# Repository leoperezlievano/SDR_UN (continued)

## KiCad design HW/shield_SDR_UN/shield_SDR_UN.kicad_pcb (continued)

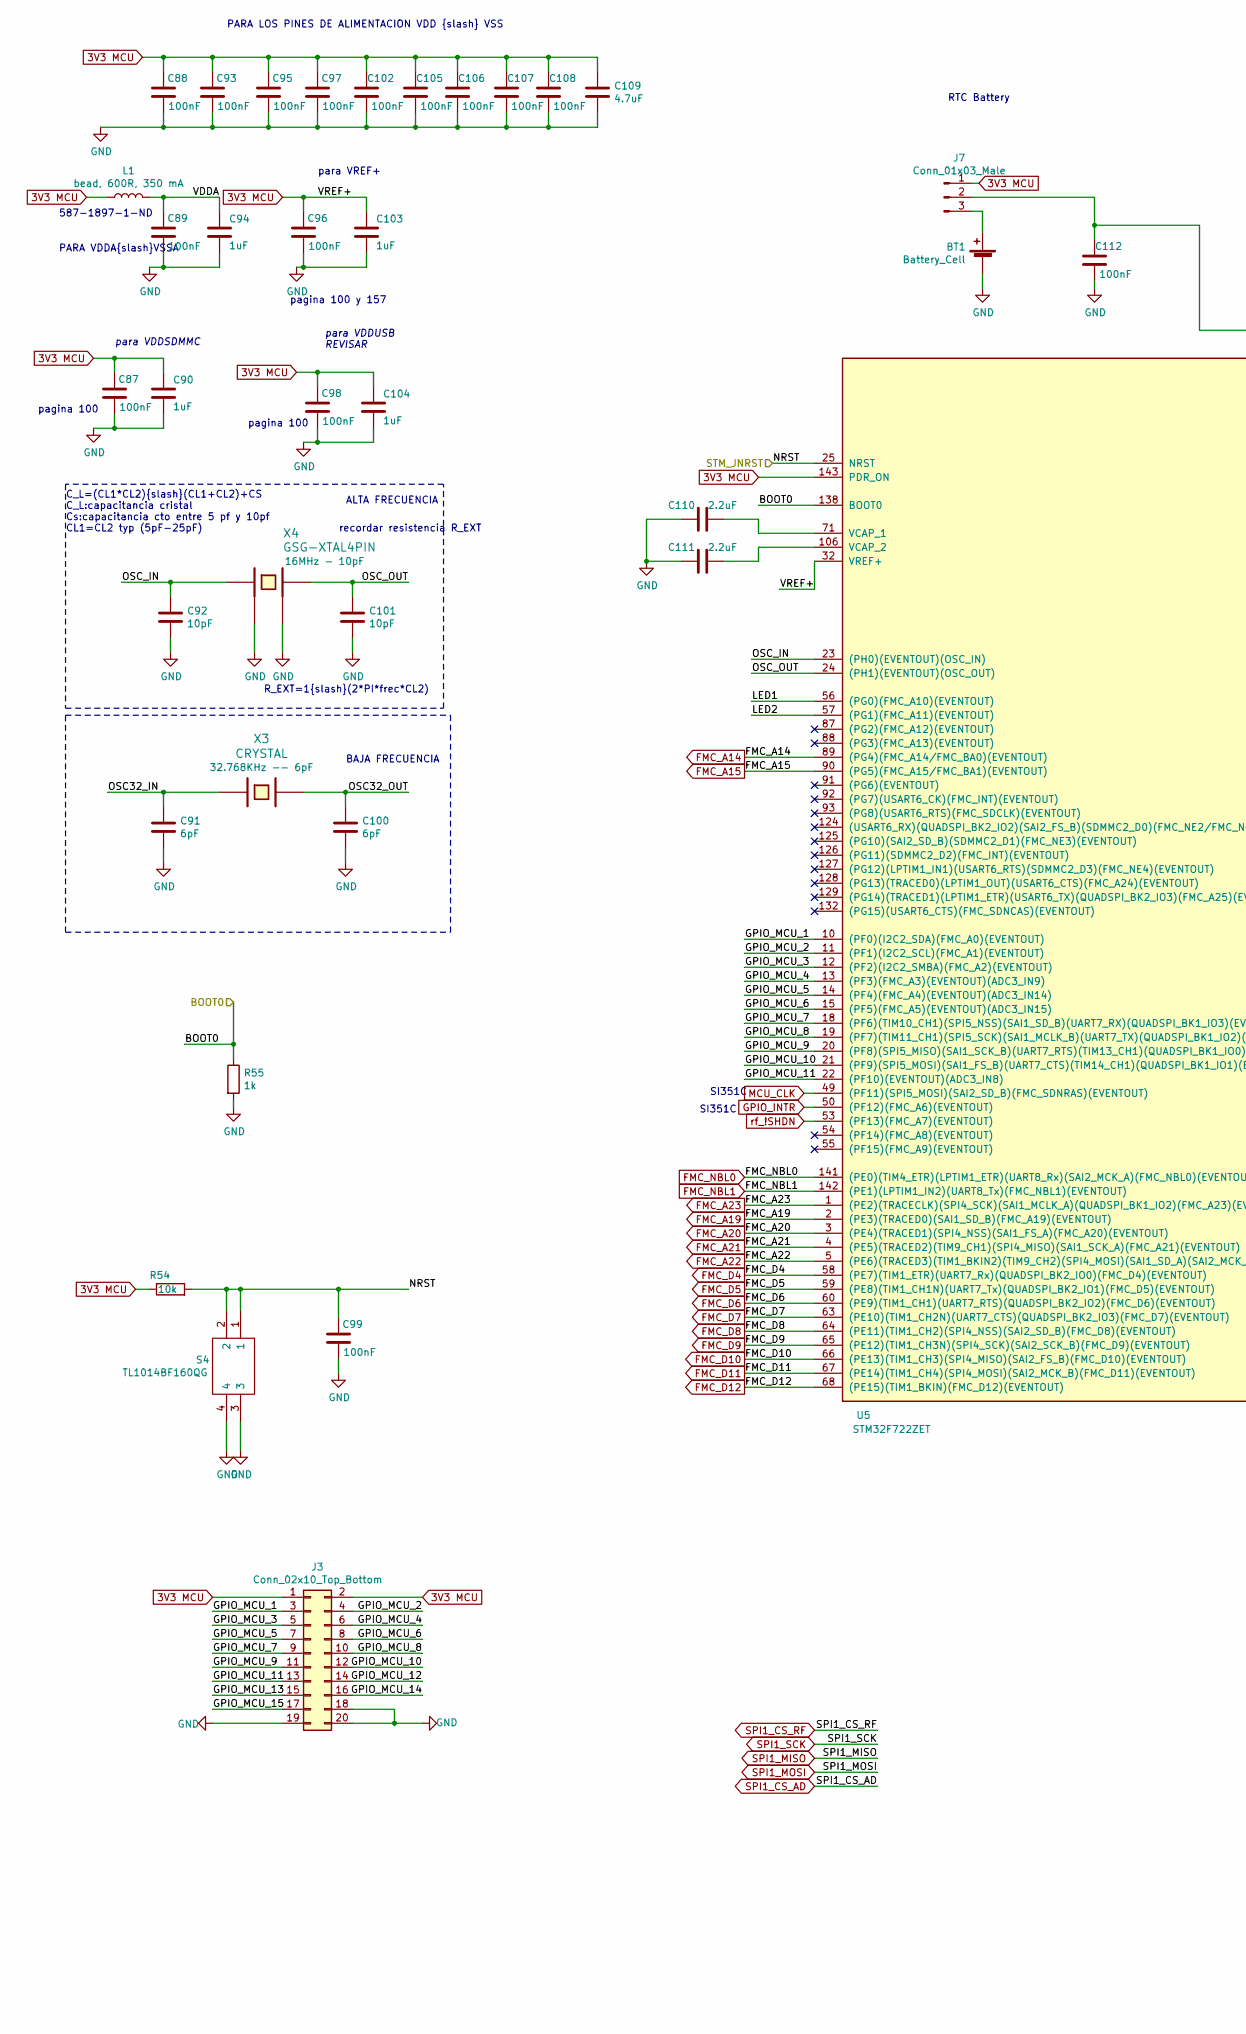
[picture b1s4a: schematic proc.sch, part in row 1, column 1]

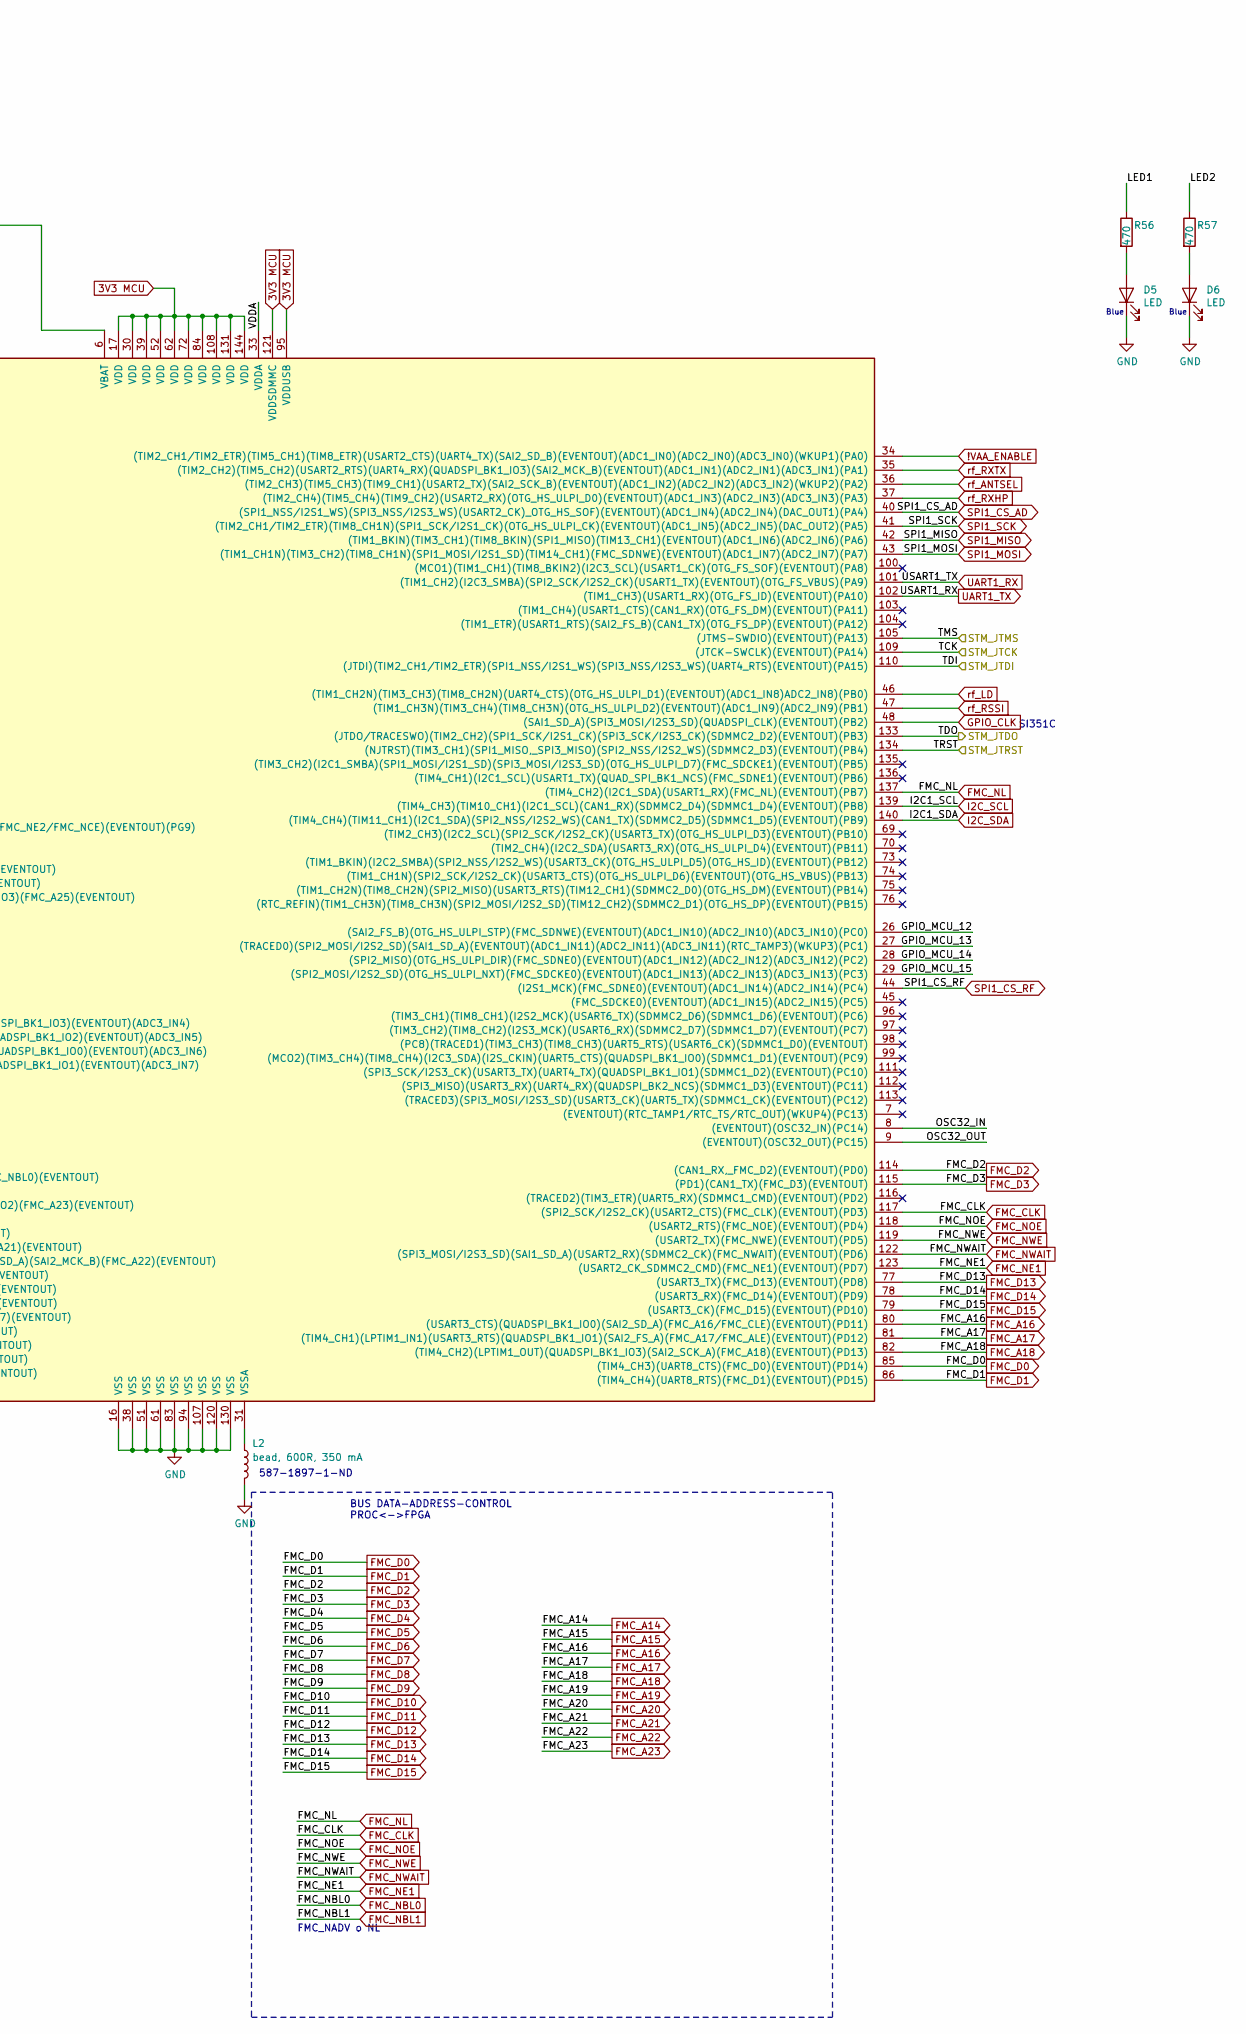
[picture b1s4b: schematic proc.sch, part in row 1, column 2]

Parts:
BT1: Battery_Cell; MPD_BK-870; digikey BK-870-ND
C87, C88, C89, C93, C95, C96, C97, C98, C99, C102, C105, C106, C107, C108, C112: 100nF; C_0603_1608Metric_Pad1.05x0.95mm_HandSolder; Digikey 1276-1000-1-ND
C90, C94, C103, C104: 1uF; C_0603_1608Metric_Pad1.05x0.95mm_HandSolder; Digikey 1276-1182-1-ND
C91, C100: 6pF; C_0603_1608Metric_Pad1.05x0.95mm_HandSolder; Digikey 1276-2133-1-ND
C92, C101: 10pF; C_0603_1608Metric_Pad1.05x0.95mm_HandSolder; Digikey 1276-1027-1-ND
C109: 4.7uF; C_0603_1608Metric_Pad1.05x0.95mm_HandSolder; Digikey 1276-1045-1-ND
C110, C111: 2.2uF; C_0603_1608Metric_Pad1.05x0.95mm_HandSolder; Digikey 1276-1085-1-ND
D5, D6: LED; LED_0805_2012Metric_Pad1.15x1.40mm_HandSolder; Digikey 160-2032-1-ND
J3: Conn_02x10_Top_Bottom; PinHeader_2x10_P2.54mm_Vertical; DIGIKEY S6106-ND
J7: Conn_01x03_Male; PinHeader_1x03_P2.54mm_Vertical
L1, L2: bead, 600R, 350 mA; L_0603_1608Metric_Pad1.05x0.95mm_HandSolder; DIGIKEY 587-1897-1-ND
R54: 10k; R_0603_1608Metric_Pad1.05x0.95mm_HandSolder; Digikey 311-10KGRCT-ND
R55: 1k; R_0603_1608Metric_Pad1.05x0.95mm_HandSolder; Digikey 311-1.00KHRCT-ND
R56, R57: 470; R_0603_1608Metric_Pad1.05x0.95mm_HandSolder; Digikey 311-470GRCT-ND
S4: TL1014BF160QG; Digikey EG5042CT-ND
U5: STM32F722ZET; LQFP-144_20x20mm_P0.5mm; digikey 497-18558-ND
X3: CRYSTAL; NX3215SA; Digikey 644-1171-1-ND
X4: GSG-XTAL4PIN; GSG-XTAL3.2x2.5mm; digikey 535-10289-1-ND

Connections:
3V3 MCU: C87.1, C88.1, C90.1, C93.1, C95.1, C96.1, C97.1, C98.1, C102.1, C103.1, C104.1, C105.1, C106.1, C107.1, C108.1, C109.1, J3.1, J3.2, J7.1, L1.1, R54.1, U5.17 (VDD), U5.30 (VDD), U5.32 (VREF+), U5.39 (VDD), U5.52 (VDD), U5.62 (VDD), U5.72 (VDD), U5.84 (VDD), U5.95 (VDDUSB), U5.108 (VDD), U5.121 (VDDSDMMC), U5.131 (VDD), U5.143 (PDR_ON), U5.144 (VDD); also elsewhere on the board
!VAA_ENABLE: U5.34 ((TIM2_CH1/TIM2_ETR)(TIM5_CH1)(TIM8_ETR)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); also elsewhere on the board
/BOOT_0: R55.1, U5.138 (BOOT0); also elsewhere on the board
/OMG_JNRST: C99.1, R54.2, S4.1, S4.2, U5.25 (NRST); also elsewhere on the board
/OMG_JTCK: U5.109 ((JTCK-SWCLK)(EVENTOUT)(PA14)); also elsewhere on the board
/OMG_JTDI: U5.110 ((JTDI)(TIM2_CH1/TIM2_ETR)(SPI1_NSS/I2S1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); also elsewhere on the board
/OMG_JTMS: U5.105 ((JTMS-SWDIO)(EVENTOUT)(PA13)); also elsewhere on the board
/OMG_JTRST: U5.134 ((NJTRST)(TIM3_CH1)(SPI1_MISO,_SPI3_MISO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); also elsewhere on the board
/STM_JTDO: U5.133 ((JTDO/TRACESWO)(TIM2_CH2)(SPI1_SCK/I2S1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); also elsewhere on the board
/proc/GPIO_MCU_1: J3.3, U5.10 ((PF0)(I2C2_SDA)(FMC_A0)(EVENTOUT))
/proc/GPIO_MCU_2: J3.4, U5.11 ((PF1)(I2C2_SCL)(FMC_A1)(EVENTOUT))
/proc/GPIO_MCU_3: J3.5, U5.12 ((PF2)(I2C2_SMBA)(FMC_A2)(EVENTOUT))
/proc/GPIO_MCU_4: J3.6, U5.13 ((PF3)(FMC_A3)(EVENTOUT)(ADC3_IN9))
/proc/GPIO_MCU_5: J3.7, U5.14 ((PF4)(FMC_A4)(EVENTOUT)(ADC3_IN14))
/proc/GPIO_MCU_6: J3.8, U5.15 ((PF5)(FMC_A5)(EVENTOUT)(ADC3_IN15))
/proc/GPIO_MCU_7: J3.9, U5.18 ((PF6)(TIM10_CH1)(SPI5_NSS)(SAI1_SD_B)(U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)
/proc/GPIO_MCU_8: J3.10, U5.19 ((PF7)(TIM11_CH1)(SPI5_SCK)(SAI1_MCLK_B)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)
/proc/GPIO_MCU_9: J3.11, U5.20 ((PF8)(SPI5_MISO)(SAI1_SCK_B)(UART7_RTS)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)
/proc/GPIO_MCU_10: J3.12, U5.21 ((PF9)(SPI5_MOSI)(SAI1_FS_B)(UART7_CTS)(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)
/proc/GPIO_MCU_11: J3.13, U5.22 ((PF10)(EVENTOUT)(ADC3_IN8))
/proc/GPIO_MCU_12: J3.14, U5.26 ((SAI2_FS_B)(OTG_HS_ULPI_STP)(FMC_SDNWE)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)
/proc/GPIO_MCU_13: J3.15, U5.27 ((TRACED0)(SPI2_MOSI/I2S2_SD)(SAI1_SD_A)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)
/proc/GPIO_MCU_14: J3.16, U5.28 ((SPI2_MISO)(OTG_HS_ULPI_DIR)(FMC_SDNE0)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)
/proc/GPIO_MCU_15: J3.17, U5.29 ((SPI2_MOSI/I2S2_SD)(OTG_HS_ULPI_NXT)(FM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)
/proc/LED1: R56.1, U5.56 ((PG0)(FMC_A10)(EVENTOUT))
/proc/LED2: R57.1, U5.57 ((PG1)(FMC_A11)(EVENTOUT))
/proc/OSC32_IN: C91.1, U5.8 ((EVENTOUT)(OSC32_IN)(PC14)), X3.1
/proc/OSC32_OUT: C100.1, U5.9 ((EVENTOUT)(OSC32_OUT)(PC15)), X3.2
/proc/OSC_IN: C92.1, U5.23 ((PH0)(EVENTOUT)(OSC_IN)), X4.1
/proc/OSC_OUT: C101.1, U5.24 ((PH1)(EVENTOUT)(OSC_OUT)), X4.3
/proc/VDDA: C89.1, C94.1, L1.2, U5.33 (VDDA)
FMC_A14: U5.89 ((PG4)(FMC_A14/FMC_BA0)(EVENTOUT)); also elsewhere on the board
FMC_A15: U5.90 ((PG5)(FMC_A15/FMC_BA1)(EVENTOUT)); also elsewhere on the board
FMC_A16: U5.80 ((USART3_CTS)(QUADSPI_BK1_IO0)(SAI2_SD_A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); also elsewhere on the board
FMC_A17: U5.81 ((TIM4_CH1)(LPTIM1_IN1)(USART3_RTS)(QUAD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); also elsewhere on the board
FMC_A18: U5.82 ((TIM4_CH2)(LPTIM1_OUT)(QUADSPI_BK1_IO3)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); also elsewhere on the board
FMC_A19: U5.2 ((PE3)(TRACED0)(SAI1_SD_B)(FMC_A19)(EVEN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); also elsewhere on the board
FMC_A20: U5.3 ((PE4)(TRACED1)(SPI4_NSS)(SAI1_FS_A)(FMC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); also elsewhere on the board
FMC_A21: U5.4 ((PE5)(TRACED2)(TIM9_CH1)(SPI4_MISO)(SAI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); also elsewhere on the board
FMC_A22: U5.5 ((PE6)(TRACED3)(TIM1_BKIN2)(TIM9_CH2)(SP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); also elsewhere on the board
FMC_A23: U5.1 ((PE2)(TRACECLK)(SPI4_SCK)(SAI1_MCLK_A)(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); also elsewhere on the board
FMC_CLK: U5.117 ((SPI2_SCK/I2S2_CK)(USART2_CTS)(FMC_CLK)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); also elsewhere on the board
FMC_D0: U5.85 ((TIM4_CH3)(UART8_CTS)(FMC_D0)(EVENTOUT)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); also elsewhere on the board
FMC_D1: U5.86 ((TIM4_CH4)(UART8_RTS)(FMC_D1)(EVENTOUT)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); also elsewhere on the board
FMC_D2: U5.114 ((CAN1_RX,_FMC_D2)(EVENTOUT)(PD0)); also elsewhere on the board
FMC_D3: U5.115 ((PD1)(CAN1_TX)(FMC_D3)(EVENTOUT)); also elsewhere on the board
FMC_D4: U5.58 ((PE7)(TIM1_ETR)(UART7_Rx)(QUADSPI_BK2_I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); also elsewhere on the board
FMC_D5: U5.59 ((PE8)(TIM1_CH1N)(UART7_Tx)(QUADSPI_BK2_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); also elsewhere on the board
FMC_D6: U5.60 ((PE9)(TIM1_CH1)(UART7_RTS)(QUADSPI_BK2_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); also elsewhere on the board
FMC_D7: U5.63 ((PE10)(TIM1_CH2N)(UART7_CTS)(QUADSPI_BK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); also elsewhere on the board
FMC_D8: U5.64 ((PE11)(TIM1_CH2)(SPI4_NSS)(SAI2_SD_B)(F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); also elsewhere on the board
FMC_D9: U5.65 ((PE12)(TIM1_CH3N)(SPI4_SCK)(SAI2_SCK_B)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); also elsewhere on the board
FMC_D10: U5.66 ((PE13)(TIM1_CH3)(SPI4_MISO)(SAI2_FS_B)(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); also elsewhere on the board
FMC_D11: U5.67 ((PE14)(TIM1_CH4)(SPI4_MOSI)(SAI2_MCK_B)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); also elsewhere on the board
FMC_D12: U5.68 ((PE15)(TIM1_BKIN)(FMC_D12)(EVENTOUT)); also elsewhere on the board
FMC_D13: U5.77 ((USART3_TX)(FMC_D13)(EVENTOUT)(PD8)); also elsewhere on the board
FMC_D14: U5.78 ((USART3_RX)(FMC_D14)(EVENTOUT)(PD9)); also elsewhere on the board
FMC_D15: U5.79 ((USART3_CK)(FMC_D15)(EVENTOUT)(PD10)); also elsewhere on the board
FMC_NBL0: U5.141 ((PE0)(TIM4_ETR)(LPTIM1_ETR)(UART8_Rx)(S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); also elsewhere on the board
FMC_NBL1: U5.142 ((PE1)(LPTIM1_IN2)(UART8_Tx)(FMC_NBL1)(E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); also elsewhere on the board
FMC_NE1: U5.123 ((USART2_CK_SDMMC2_CMD)(FMC_NE1)(EVENTOU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); also elsewhere on the board
FMC_NL: U5.137 ((TIM4_CH2)(I2C1_SDA)(USART1_RX)(FMC_NL)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); also elsewhere on the board
FMC_NOE: U5.118 ((USART2_RTS)(FMC_NOE)(EVENTOUT)(PD4)); also elsewhere on the board
FMC_NWAIT: U5.122 ((SPI3_MOSI/I2S3_SD)(SAI1_SD_A)(USART2_R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); also elsewhere on the board
FMC_NWE: U5.119 ((USART2_TX)(FMC_NWE)(EVENTOUT)(PD5)); also elsewhere on the board
GND: BT1.2 (-), C87.2, C88.2, C89.2, C90.2, C91.2, C92.2, C93.2, C94.2, C95.2, C96.2, C97.2, C98.2, C99.2, C100.2, C101.2, C102.2, C103.2, C104.2, C105.2, C106.2, C107.2, C108.2, C109.2, C110.1, C111.1, C112.2, D5.1 (K), D6.1 (K), J3.18, J3.19, J3.20, L2.2, R55.2, S4.3, S4.4, U5.16 (VSS), U5.38 (VSS), U5.51 (VSS), U5.61 (VSS), U5.83 (VSS), U5.94 (VSS), U5.107 (VSS), U5.120 (VSS), U5.130 (VSS), X4.2, X4.4; also elsewhere on the board
GPIO_CLK: U5.48 ((SAI1_SD_A)(SPI3_MOSI/I2S3_SD)(QUADSPI_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); also elsewhere on the board
GPIO_INTR: U5.50 ((PF12)(FMC_A6)(EVENTOUT)); also elsewhere on the board
I2C_SCL: U5.139 ((TIM4_CH3)(TIM10_CH1)(I2C1_SCL)(CAN1_RX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); also elsewhere on the board
I2C_SDA: U5.140 ((TIM4_CH4)(TIM11_CH1)(I2C1_SDA)(SPI2_NS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); also elsewhere on the board
MCU_CLK: U5.49 ((PF11)(SPI5_MOSI)(SAI2_SD_B)(FMC_SDNRAS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); also elsewhere on the board
unnamed: BT1.1 (+), J7.3
unnamed: C110.2, U5.71 (VCAP_1)
unnamed: C111.2, U5.106 (VCAP_2)
unnamed: C112.1, J7.2, U5.6 (VBAT)
unnamed: D5.2 (A), R56.2
unnamed: D6.2 (A), R57.2
unnamed: L2.1, U5.31 (VSSA)
SPI1_CS_AD: U5.40 ((SPI1_NSS/I2S1_WS)(SPI3_NSS/I2S3_WS)(US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); also elsewhere on the board
SPI1_CS_RF: U5.44 ((I2S1_MCK)(FMC_SDNE0)(EVENTOUT)(ADC1_IN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); also elsewhere on the board
SPI1_MISO: U5.42 ((TIM1_BKIN)(TIM3_CH1)(TIM8_BKIN)(SPI1_M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); also elsewhere on the board
SPI1_MOSI: U5.43 ((TIM1_CH1N)(TIM3_CH2)(TIM8_CH1N)(SPI1_M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); also elsewhere on the board
SPI1_SCK: U5.41 ((TIM2_CH1/TIM2_ETR)(TIM8_CH1N)(SPI1_SCK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); also elsewhere on the board
UART1_RX: U5.101 ((TIM1_CH2)(I2C3_SMBA)(SPI2_SCK/I2S2_CK)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); also elsewhere on the board
UART1_TX: U5.102 ((TIM1_CH3)(USART1_RX)(OTG_FS_ID)(EVENTO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); also elsewhere on the board
rf_!SHDN: U5.53 ((PF13)(FMC_A7)(EVENTOUT)); also elsewhere on the board
rf_ANTSEL: U5.36 ((TIM2_CH3)(TIM5_CH3)(TIM9_CH1)(USART2_T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); also elsewhere on the board
rf_LD: U5.46 ((TIM1_CH2N)(TIM3_CH3)(TIM8_CH2N)(UART4_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); also elsewhere on the board
rf_RSSI: U5.47 ((TIM1_CH3N)(TIM3_CH4)(TIM8_CH3N)(OTG_HS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); also elsewhere on the board
rf_RXHP: U5.37 ((TIM2_CH4)(TIM5_CH4)(TIM9_CH2)(USART2_R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); also elsewhere on the board
rf_RXTX: U5.35 ((TIM2_CH2)(TIM5_CH2)(USART2_RTS)(UART4_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); also elsewhere on the board

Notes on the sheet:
PARA LOS PINES DE ALIMENTACION VDD {slash} VSS
PARA VDDA{slash}VSSA
pagina 100 y 157
para VREF+
para VDDSDMMC
pagina 100
para VDDUSB REVISAR
C_L=(CL1*CL2){slash}(CL1+CL2)+CS C_L:capacitancia cristal Cs:capacitancia cto entre 5 pf y 10pf CL1=CL2 typ (5pF-25pF)
ALTA FRECUENCIA
BAJA FRECUENCIA
recordar resistencia R_EXT
R_EXT=1{slash}(2*PI*frec*CL2)
RTC Battery
BUS DATA-ADDRESS-CONTROL PROC<->FPGA
587-1897-1-ND
Blue
SI351C
FMC_NADV o NL

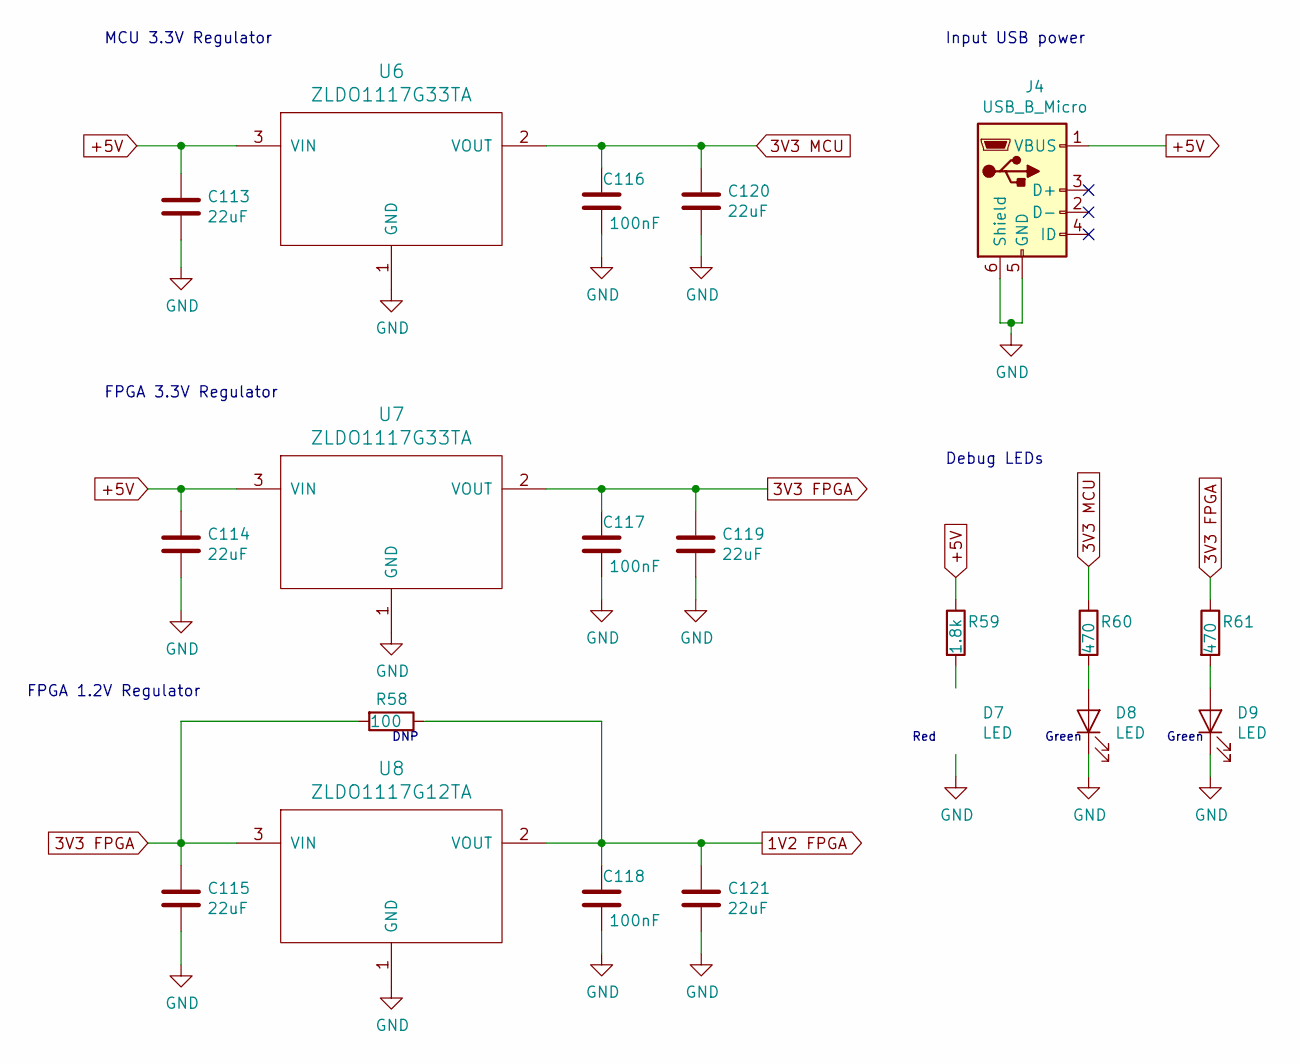
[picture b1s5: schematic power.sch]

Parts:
C113, C114, C115, C119, C120, C121: 22uF; R_0603_1608Metric_Pad1.05x0.95mm_HandSolder; Digikey 1276-6504-1-ND
C116, C117, C118: 100nF; C_0603_1608Metric_Pad1.05x0.95mm_HandSolder; Digikey 1276-1000-1-ND
D7: LED; LED_0805_2012Metric_Pad1.15x1.40mm_HandSolder; Digikey 160-1469-1-ND
D8, D9: LED; LED_0805_2012Metric_Pad1.15x1.40mm_HandSolder; Digikey 160-1468-1-ND
J4: USB_B_Micro; USB_Micro_B_Female_10118194-0001LF; Digikey 609-4618-1-ND
R58: 100; R_0603_1608Metric_Pad1.05x0.95mm_HandSolder; Digikey 311-100HRCT-ND
R59: 1.8k; R_0603_1608Metric_Pad1.05x0.95mm_HandSolder; Digikey 311-1.8KGRTR-ND
R60, R61: 470; R_0603_1608Metric_Pad1.05x0.95mm_HandSolder; Digikey 311-470GRCT-ND
U6, U7: ZLDO1117G33TA; SOT-223-3_TabPin2; Digikey ZLDO1117G33DICT-ND
U8: ZLDO1117G12TA; SOT-223-3_TabPin2; Digikey ZLDO1117G12DICT-ND

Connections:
1V2 FPGA: C118.1, C121.1, R58.1, U8.2 (VOUT); also elsewhere on the board
3V3 FPGA: C115.1, C117.1, C119.1, R58.2, R61.1, U7.2 (VOUT), U8.3 (VIN); also elsewhere on the board
3V3 MCU: C116.1, C120.1, R60.1, U6.2 (VOUT); also elsewhere on the board
+5V: C113.1, C114.1, J4.1 (VBUS), R59.1, U6.3 (VIN), U7.3 (VIN); also elsewhere on the board
GND: C113.2, C114.2, C115.2, C116.2, C117.2, C118.2, C119.2, C120.2, C121.2, D7.1 (K), D8.1 (K), D9.1 (K), J4.5 (GND), J4.6 (Shield), U6.1 (GND), U7.1 (GND), U8.1 (GND); also elsewhere on the board
unnamed: D7.2 (A), R59.2
unnamed: D8.2 (A), R60.2
unnamed: D9.2 (A), R61.2

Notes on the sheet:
MCU 3.3V Regulator
FPGA 3.3V Regulator
FPGA 1.2V Regulator
Input USB power
Debug LEDs
Red
Green
DNP

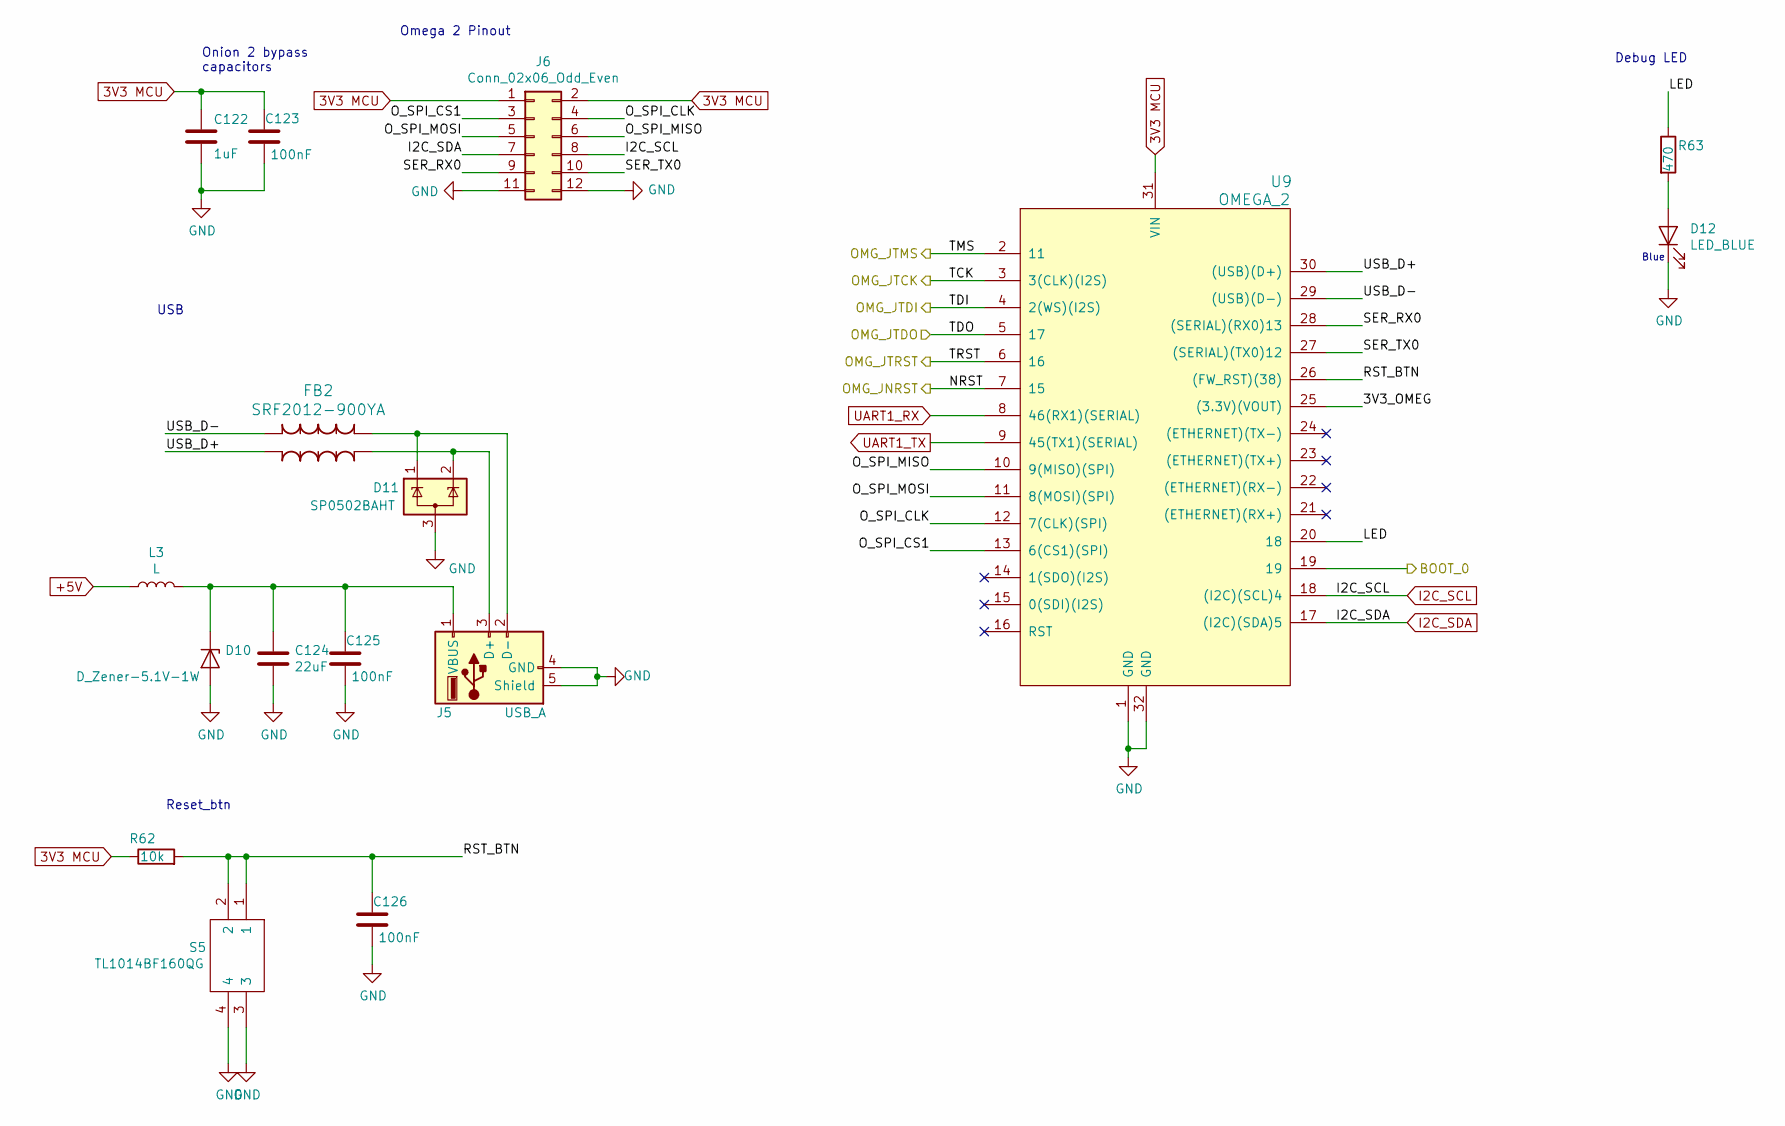
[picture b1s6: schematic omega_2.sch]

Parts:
C122: 1uF; C_0603_1608Metric_Pad1.05x0.95mm_HandSolder; Digikey 1276-1182-1-ND
C123, C125, C126: 100nF; C_0603_1608Metric_Pad1.05x0.95mm_HandSolder; Digikey 1276-1000-1-ND
C124: 22uF; R_0603_1608Metric_Pad1.05x0.95mm_HandSolder; Digikey 1276-6504-1-ND
D10: D_Zener-5.1V-1W; D_SOD-123; Digikey MMSZ5231BT1GOSCT-ND
D11: SP0502BAHT; SOT-23_Handsoldering; Digikey F2714CT-ND
D12: LED_BLUE; LED_0805_2012Metric_Pad1.15x1.40mm_HandSolder; Digikey 160-2032-1-ND
FB2: SRF2012-900YA; Digikey SRF2012-900YACT-ND
J5: USB_A; USB_A_Female_UE27AC54100; Digikey UE27AC54100-ND
J6: Conn_02x06_Odd_Even; PinHeader_2x06_P2.54mm_Vertical; Digikey 609-3219-ND
L3: L; L_0603_1608Metric_Pad1.05x0.95mm_HandSolder; Digikey 732-1593-1-ND
R62: 10k; R_0603_1608Metric_Pad1.05x0.95mm_HandSolder; Digikey 311-10KGRCT-ND
R63: 470; R_0603_1608Metric_Pad1.05x0.95mm_HandSolder; Digikey 311-470GRCT-ND
S5: TL1014BF160QG; Digikey EG5042CT-ND
U9: OMEGA_2; OMEGA2_PADS; Digikey 2070-OM-O2-ND

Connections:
3V3 MCU: C122.1, C123.1, J6.1, J6.2, R62.1, U9.31 (VIN); also elsewhere on the board
+5V: L3.1; also elsewhere on the board
/BOOT_0: U9.19; also elsewhere on the board
/FPGA_JTDO: U9.5 (17); also elsewhere on the board
/OMG_JNRST: U9.7 (15); also elsewhere on the board
/OMG_JTCK: U9.3 (3(CLK)(I2S)); also elsewhere on the board
/OMG_JTDI: U9.4 (2(WS)(I2S)); also elsewhere on the board
/OMG_JTMS: U9.2 (11); also elsewhere on the board
/OMG_JTRST: U9.6 (16); also elsewhere on the board
/omega_2/3V3_OMEG: U9.25 ((3.3V)(VOUT))
/omega_2/LED: R63.1, U9.20 (18)
/omega_2/O_SPI_CLK: J6.4, U9.12 (7(CLK)(SPI))
/omega_2/O_SPI_CS1: J6.3, U9.13 (6(CS1)(SPI))
/omega_2/O_SPI_MISO: J6.6, U9.10 (9(MISO)(SPI))
/omega_2/O_SPI_MOSI: J6.5, U9.11 (8(MOSI)(SPI))
/omega_2/RST_BTN: C126.1, R62.2, S5.1, S5.2, U9.26 ((FW_RST)(38))
/omega_2/SER_RX0: J6.9, U9.28 ((SERIAL)(RX0)13)
/omega_2/SER_TX0: J6.10, U9.27 ((SERIAL)(TX0)12)
/omega_2/USB_D+: FB2.4, U9.30 ((USB)(D+))
/omega_2/USB_D-: FB2.1, U9.29 ((USB)(D-))
GND: C122.2, C123.2, C124.2, C125.2, C126.2, D10.2 (A), D11.3 (A), D12.1 (K), J5.4 (GND), J5.5 (Shield), J6.11, J6.12, S5.3, S5.4, U9.1 (GND), U9.32 (GND); also elsewhere on the board
I2C_SCL: J6.8, U9.18 ((I2C)(SCL)4); also elsewhere on the board
I2C_SDA: J6.7, U9.17 ((I2C)(SDA)5); also elsewhere on the board
unnamed: C124.1, C125.1, D10.1 (K), J5.1 (VBUS), L3.2
unnamed: D11.1 (K), FB2.2, J5.2 (D-)
unnamed: D11.2 (K), FB2.3, J5.3 (D+)
unnamed: D12.2 (A), R63.2
UART1_RX: U9.8 (46(RX1)(SERIAL)); also elsewhere on the board
UART1_TX: U9.9 (45(TX1)(SERIAL)); also elsewhere on the board

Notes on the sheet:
Onion 2 bypass capacitors
USB
Omega 2 Pinout
Reset_btn
Debug LED
Blue

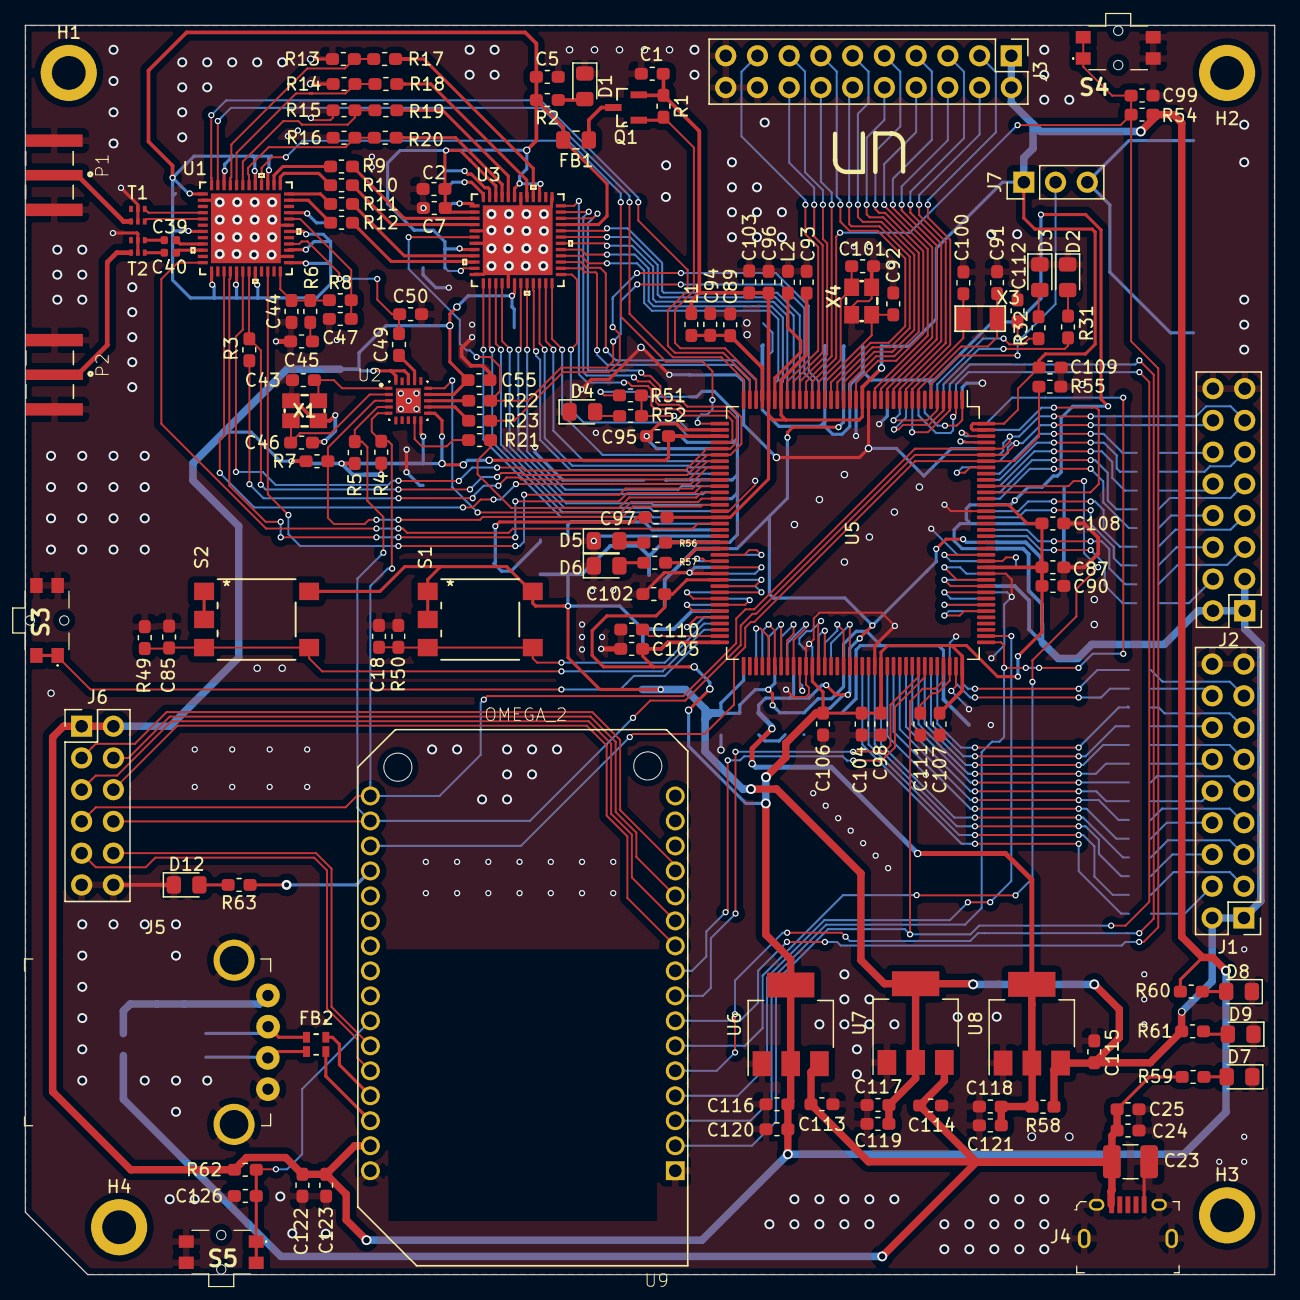
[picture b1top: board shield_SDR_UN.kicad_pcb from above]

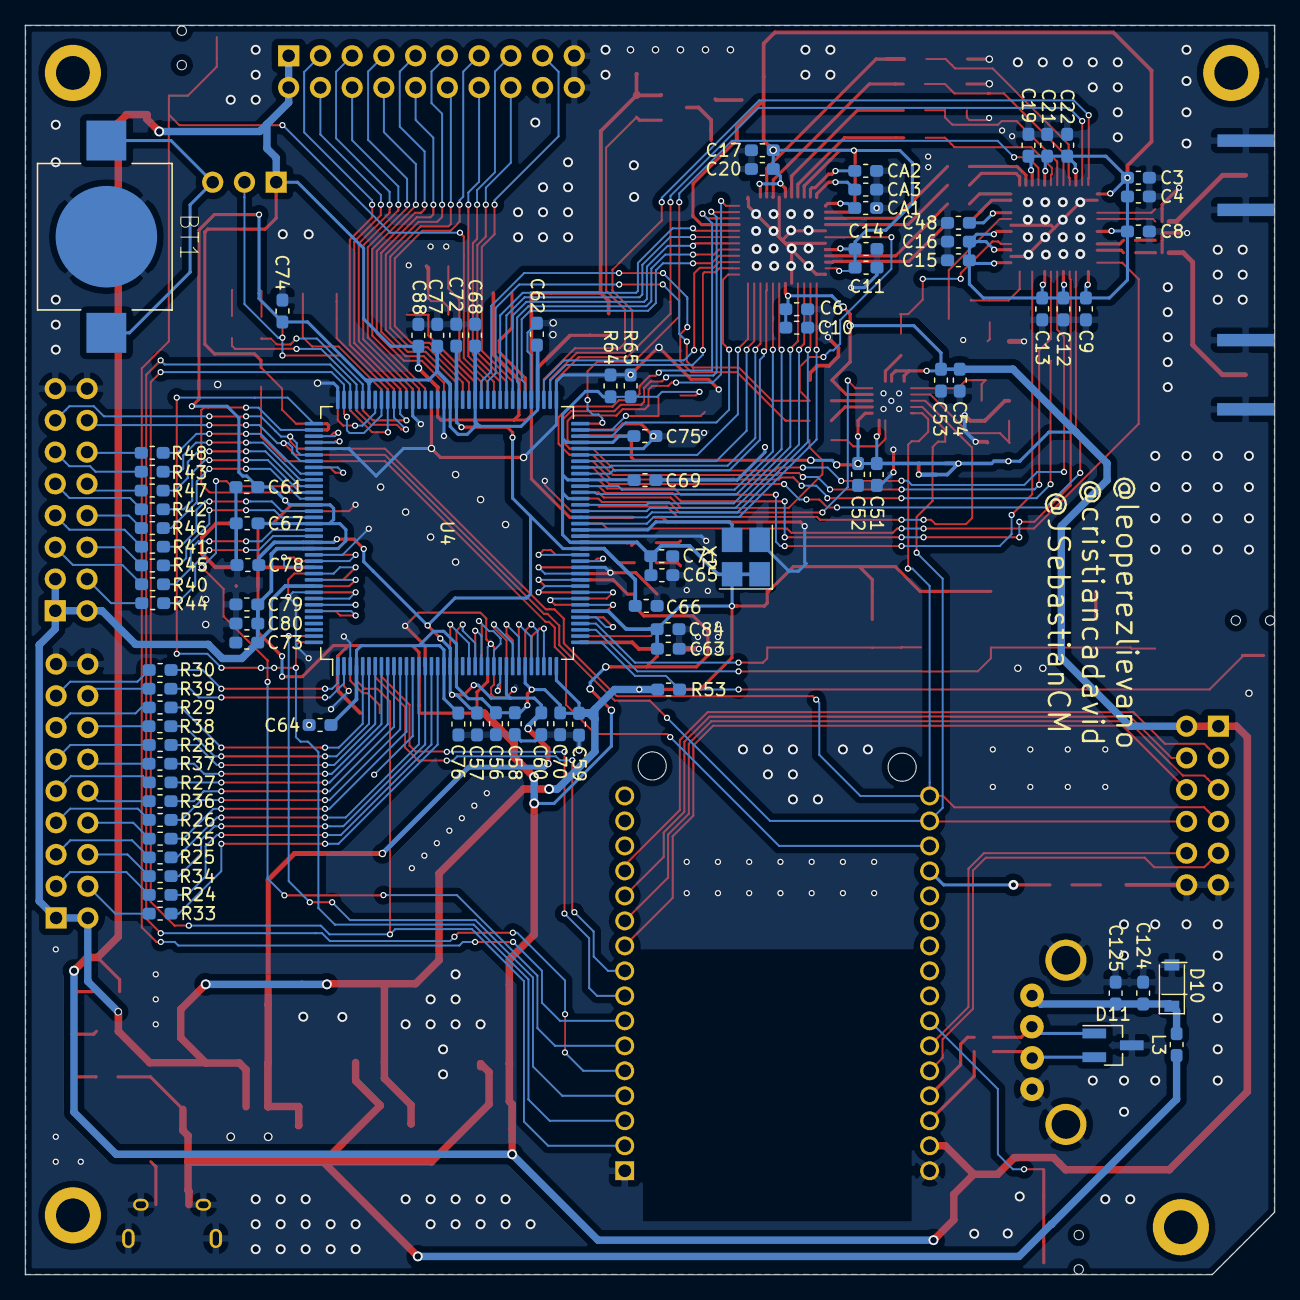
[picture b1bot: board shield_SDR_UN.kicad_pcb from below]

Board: 2 copper layers, 100.0 x 100.0 mm, 227 parts (86 on the bottom side), 230 nets.

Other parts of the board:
C23: 220uF; R_1210_3225Metric_Pad1.42x2.65mm_HandSolder
C24: 100nF; C_0603_1608Metric_Pad1.05x0.95mm_HandSolder
C25: 1nF; C_0603_1608Metric_Pad1.05x0.95mm_HandSolder

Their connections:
+5V: C23.1, C24.1, C25.1; also elsewhere on the board
GND: C23.2, C24.2, C25.2; also elsewhere on the board

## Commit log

2019-04-24 First commit - Repository created
2019-04-29 Subsystems sheets created
2019-05-02 ADC schematic done.
2019-05-04 proc schematic done test.
2019-05-07 adicion potencia usb y osc procesador
2019-05-07 MAX2830 Symbol/Footprint created
2019-05-09 Onion 2 routed
2019-05-13 Se añade el esquema de la FPGA
2019-05-14 FPGA-ADC connection
2019-05-14 STM32 connection updated
2019-05-14 Voltage regulators updated
2019-05-14 LED-PROC
2019-05-16 data bus proc-fpga
2019-05-16 Footprint of voltaje regulators edited
2019-05-20 bus-v2 proc-fpga
2019-05-20 algunos footprint
2019-05-20 algunos footprint_v2
2019-05-21 RF-Frontend balun
2019-05-22 se agrego el chip multirelojes
2019-05-22 Footprints added for C and R
2019-05-22 Footprints updated
2019-05-23 OTRA VES FOOTPRINT
2019-05-23 OTRA VES FOOTPRINT_v1
2019-05-23 RF-Front-end connections
2019-05-23 OTRA VES FOOTPRINT_v2
2019-05-24 JTAG routed
2019-05-24 i2c_complete
2019-05-25 JTAG routed_2
2019-05-25 Schematic finished
2019-05-27 organizacion PCB
2019-05-27 Omega 2 PCB
2019-05-27 organizacion PCB_V2
2019-05-27 ADC PCB
2019-05-28 organizacion PCB_V3
2019-05-28 Capacitors of RF front-end edited, components placed in the PCB
2019-05-28 organizacion PCB_V4
2019-05-28 PCB :)
2019-05-28 PCB route V1
2019-05-29 PCB route V2
2019-05-29 PCB routing
2019-05-29 PCB route V3
2019-05-29 PCB, Power stage routed
2019-05-30 PCB route V4
2019-05-30 PCB_VERSION2
2019-05-30 Switchs modified
2019-05-31 PCB_rout_1
2019-06-04 PCB_rout_2
2019-06-05 Partnumbers modified
2019-06-05 Partnumbers modified_2
2019-06-06 design rules corrections
2019-06-06 Bill of materials updated
2019-06-07 generate gerber files test
2019-06-07 generate gerber files test_2
2019-06-07 generate gerber files test_3
2019-06-09 Gerber files created
2019-07-25 Libraries, Onion Omega files and FPGA blinker added
2019-07-25 Se añade PDF del esquemático
2019-07-25 fotos y pdf de la pcb
2019-07-25 STM32F7 Blink added
2019-07-25 agrego xc3sprog
2019-07-25 fotos compilacion openocd y xc3sprog
2019-07-25 Final Software commit
2019-07-26 Add gif file
    add gif file
